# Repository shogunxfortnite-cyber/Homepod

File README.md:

# Homepod

## What is it 
Its a tiny homepod for for a smart home. 

It consists of a esp32 s3 n16r8 as its main board.

A 2.8inch touch TFT display for smooth navigation.

Also a joystick module for extra navigation specs.

### **Bill of Materials (BOM)**

| Item # | Component Name | Description | Qty | Est. Unit Price | Total Price | Primary Link | Alternative Link |
| :---: | :--- | :--- | :---: | :---: | :---: | :---: | :---: |
| **1** | K023 Joystick Module | Analog 2-axis joystick with push button | 1 | $0.50 | $0.50 | https://robocraze.com/products/joystick-module?variant=40192421527705c | 
| **2** | ESP32-S3 N16R8 | Development board (16MB Flash / 8MB PSRAM) | 1 | $10.00 | $10.00 | https://robocraze.com/products/7semi-esp32-s3-dev-boardc-1-n8r8-wifi-bluetooth-dual-usb-c-rgb-led?variant=48519036272864|
| **3** | SmartElex 2.8" TFT Touch Screen | Display module with XPT2046 touch interface | 1 | $10.00 | $10.00 | https://robocraze.com/products/smartelex-xpt2046-2-8-inch-tft-lcd-resistive-touch-display-240-320?variant=48481353203936 |
| **4** | Custom PCB | Main circuit board for project assembly | 1 | $9.00 | $9.00 |  https://robu.in/|
| | | **Total Price:** | | | **$29.50** | | |

## Uniqueness

It has a special idle mode and menu in it.

It allows the users to connect to the wifi without editing the code.

## Guide
So for this project we would be using Kicad for designing the PCB.

## Schematic 

The connections for the schematic are like this.

##### Symbols
For the esp 32 s3 we would be using the symbol of ESP32S3 Devkit C1.

For the TFT we will use Conn_01x14_Pin.

For the joystick we will use Conn_01x05_Pin.

## Footprint assignment

The assignments are shown here.

## PCB and Routing 

The PCB is routed like this as shown here.

## 3D view

# Built for half life

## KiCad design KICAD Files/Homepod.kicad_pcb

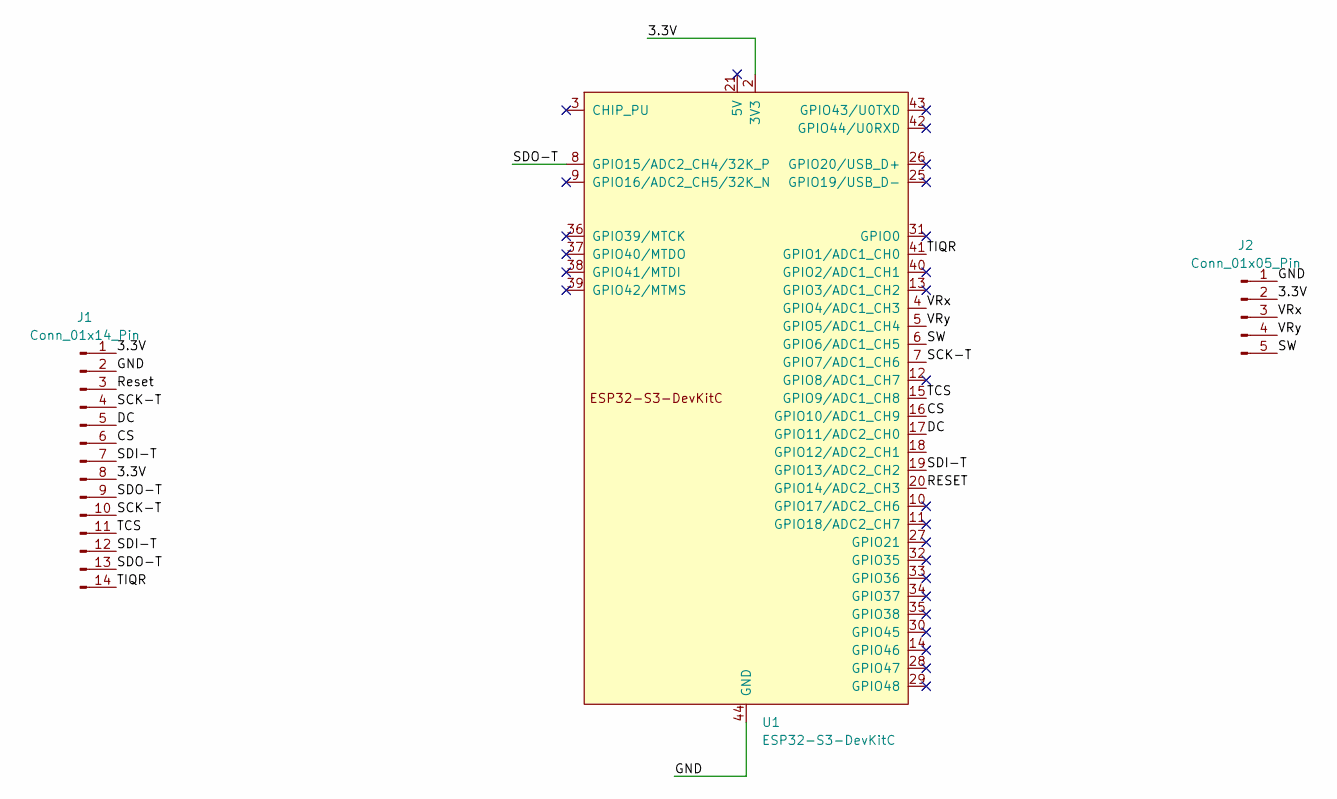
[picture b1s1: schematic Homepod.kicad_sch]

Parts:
J1: Conn_01x14_Pin; PinHeader_1x14_P2.54mm_Vertical
J2: Conn_01x05_Pin; PinHeader_1x05_P2.54mm_Vertical
U1: ESP32-S3-DevKitC

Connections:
/3.3V: J1.1, J1.8, J2.2, U1.1 (3V3), U1.2 (3V3)
/CS: J1.6, U1.16 (GPIO10/ADC1_CH9)
/DC: J1.5, U1.17 (GPIO11/ADC2_CH0)
/GND: J1.2, J2.1, U1.22 (GND), U1.23 (GND), U1.24 (GND), U1.44 (GND)
/RESET: U1.20 (GPIO14/ADC2_CH3)
/Reset: J1.3
/SCK-T: J1.4, J1.10, U1.7 (GPIO7/ADC1_CH6)
/SDI-T: J1.7, J1.12, U1.19 (GPIO13/ADC2_CH2)
/SDO-T: J1.9, J1.13, U1.8 (GPIO15/ADC2_CH4/32K_P)
/SW: J2.5, U1.6 (GPIO6/ADC1_CH5)
/TCS: J1.11, U1.15 (GPIO9/ADC1_CH8)
/TIQR: J1.14, U1.41 (GPIO1/ADC1_CH0)
/VRx: J2.3, U1.4 (GPIO4/ADC1_CH3)
/VRy: J2.4, U1.5 (GPIO5/ADC1_CH4)

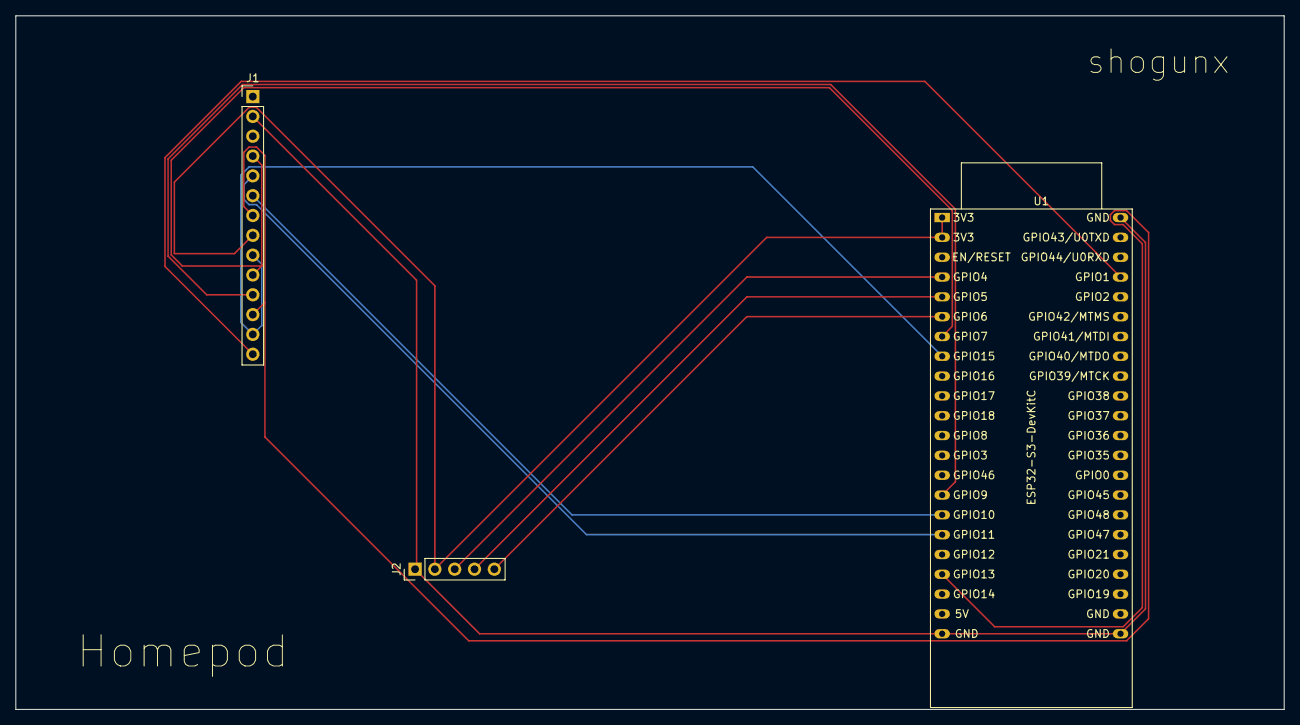
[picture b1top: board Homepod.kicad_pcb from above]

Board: 2 copper layers, 162.6 x 88.9 mm, 3 parts (0 on the bottom side), 12 nets.
